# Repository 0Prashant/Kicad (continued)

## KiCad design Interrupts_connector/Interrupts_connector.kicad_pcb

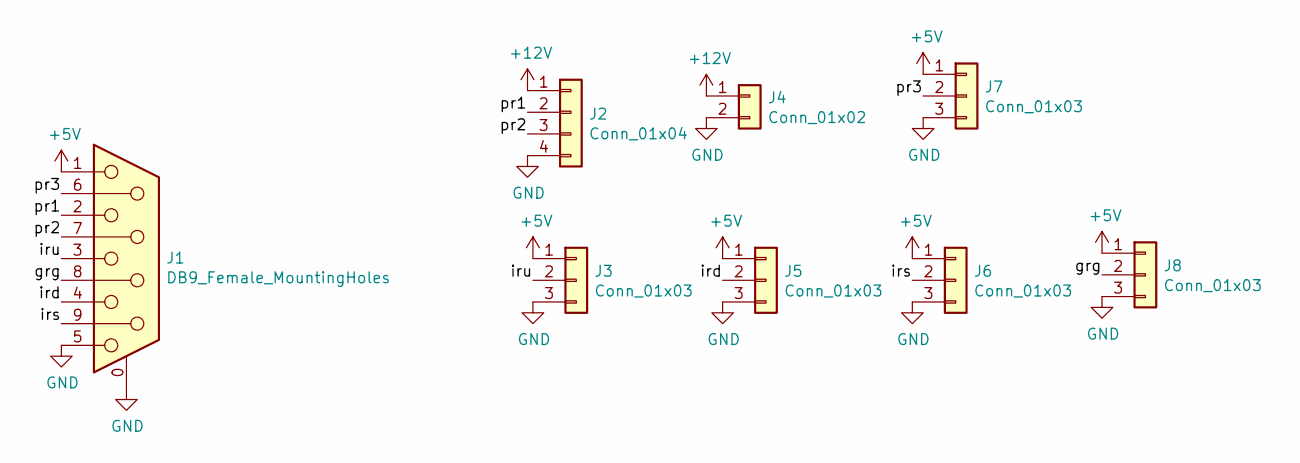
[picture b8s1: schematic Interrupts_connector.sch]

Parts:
J1: DB9_Female_MountingHoles; Connector_DB_9
J2: Conn_01x04; JST_XH_B04B-XH-A_04x2.50mm_Straight
J3, J5, J6, J7, J8: Conn_01x03; JST_XH_B03B-XH-A_03x2.50mm_Straight
J4: Conn_01x02; JST_XH_B02B-XH-A_02x2.50mm_Straight

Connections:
+5V: J1.1, J3.1, J5.1, J6.1, J7.1, J8.1
+12V: J2.1, J4.1
/grg: J1.8, J8.2
/ird: J1.4, J5.2
/irs: J1.9, J6.2
/iru: J1.3, J3.2
/pr1: J1.2, J2.2
/pr2: J1.7, J2.3
/pr3: J1.6, J7.2
GND: J1.0 (PAD), J1.5, J2.4, J3.3, J4.2, J5.3, J6.3, J7.3, J8.3

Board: 2 copper layers, 8 parts (0 on the bottom side), 10 nets, no tracks yet.

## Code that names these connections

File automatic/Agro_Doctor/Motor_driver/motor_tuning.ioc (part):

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Mcu.Name=STM32F407V(E-G)Tx
Mcu.Package=LQFP100
Mcu.UserName=STM32F407VGTx
PA1.GPIOParameters=GPIO_Label
PA1.GPIO_Label=E2_CHB
PA1.Signal=S_TIM2_CH2
PA10.GPIOParameters=GPIO_Label
PA10.GPIO_Label=SERVO_PWM
PA10.Signal=S_TIM1_CH3
PA13.Mode=Trace_Asynchronous_SW
PA13.Signal=SYS_JTMS-SWDIO
PA14.Mode=Trace_Asynchronous_SW
PA14.Signal=SYS_JTCK-SWCLK
PA2.Mode=Asynchronous
PA2.Signal=USART2_TX
PA3.Mode=Asynchronous
PA3.Signal=USART2_RX
PA5.GPIOParameters=GPIO_Label
PA5.GPIO_Label=E2_CHA
PA5.Signal=S_TIM2_CH1_ETR
PA6.GPIOParameters=GPIO_Label
PA6.GPIO_Label=E3_CHA
PA6.Signal=S_TIM3_CH1
PA7.GPIOParameters=GPIO_Label
PA7.GPIO_Label=E3_CHB
PA7.Signal=S_TIM3_CH2
PB10.Mode=I2C
PB10.Signal=I2C2_SCL
PB11.Mode=I2C
PB11.Signal=I2C2_SDA
PB3.Mode=Trace_Asynchronous_SW
PB3.Signal=SYS_JTDO-SWO
PB6.Mode=Asynchronous
PB6.Signal=USART1_TX
PB7.Mode=Asynchronous
PB7.Signal=USART1_RX
PB8.Mode=I2C
PB8.Signal=I2C1_SCL
PB9.Mode=I2C
PB9.Signal=I2C1_SDA
PC10.Mode=Asynchronous
PC10.Signal=USART3_TX
PC11.Mode=Asynchronous
PC11.Signal=USART3_RX
PC6.GPIOParameters=GPIO_Label
PC6.GPIO_Label=M1PWM
PC6.Signal=S_TIM8_CH1
PC7.GPIOParameters=GPIO_Label
PC7.GPIO_Label=M2PWM
PC7.Signal=S_TIM8_CH2
PC8.GPIOParameters=GPIO_Label
PC8.GPIO_Label=M3PWM
PC8.Signal=S_TIM8_CH3
PC9.GPIOParameters=GPIO_Label
PC9.GPIO_Label=M4PWM
PC9.Signal=S_TIM8_CH4
PE11.GPIOParameters=GPIO_Label
PE11.GPIO_Label=E1_CHB
PE11.Signal=S_TIM1_CH2
PE9.GPIOParameters=GPIO_Label
PE9.GPIO_Label=E1_CHA
PE9.Signal=S_TIM1_CH1
PH0-OSC_IN.Mode=HSE-External-Oscillator
PH0-OSC_IN.Signal=RCC_OSC_IN
PH1-OSC_OUT.Mode=HSE-External-Oscillator
PH1-OSC_OUT.Signal=RCC_OSC_OUT
RCC.HSE_VALUE=8000000
RCC.SYSCLKFreq_VALUE=168000000
RCC.SYSCLKSource=RCC_SYSCLKSOURCE_PLLCLK
board=STM32F4DISCOVERY
boardIOC=true

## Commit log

2018-04-20 Added all kicad work to github
2018-05-22 added circuit of automatic2018 and connection tester
2018-06-03 Added another circuit
2018-06-04 Created new schemetic for automatic
2018-06-10 Modified the automatic circuit
2018-06-18 added the jst connector
2018-06-30 Added mannual led-strip ckt
2018-07-10 added the pneumetic circuit
2018-07-24 Almost final automatic base mega + bridge
2018-07-24 Final automatic base circuits for ABU_ROBOCON_2018 completed
2018-08-01 Final for ABU_ROBOCON_2018 Automatic_Base
2018-08-07 Buck circuit also modified and pdfs also changed
2019-01-17 working on Agro_Doctor
2019-08-23 added the minor project file
